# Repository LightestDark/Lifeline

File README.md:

# Lifeline

This project aims to expand on the existing LoRa Puck guide, to make a pair of fully functioning transmitters that can display messages from the latter via oled, provide accurate GPS location up to 2 meters and even vital info on moisture, temperature and pressure to make an esitmated guess on the weather at the area and relay it.

# Lessons

I LOVED the physics behind the why in the routing it actually linked so well to my own studies, especially the low pass filtering. Despite this being my smallest pcb to date by no means was it the easiest, with cramming as efficiently each component so there was enough room as well as keeping enough space to allow the RF components to work properly and juggle vias everywhere it was a labour.

# Assembly

Made a simple box with plently space for antennas and display

# PCB

Ensured short efficient tracks by precise placing of components

# Schematic

Added GPS, OLED and An array of sesnors packed into a BME280

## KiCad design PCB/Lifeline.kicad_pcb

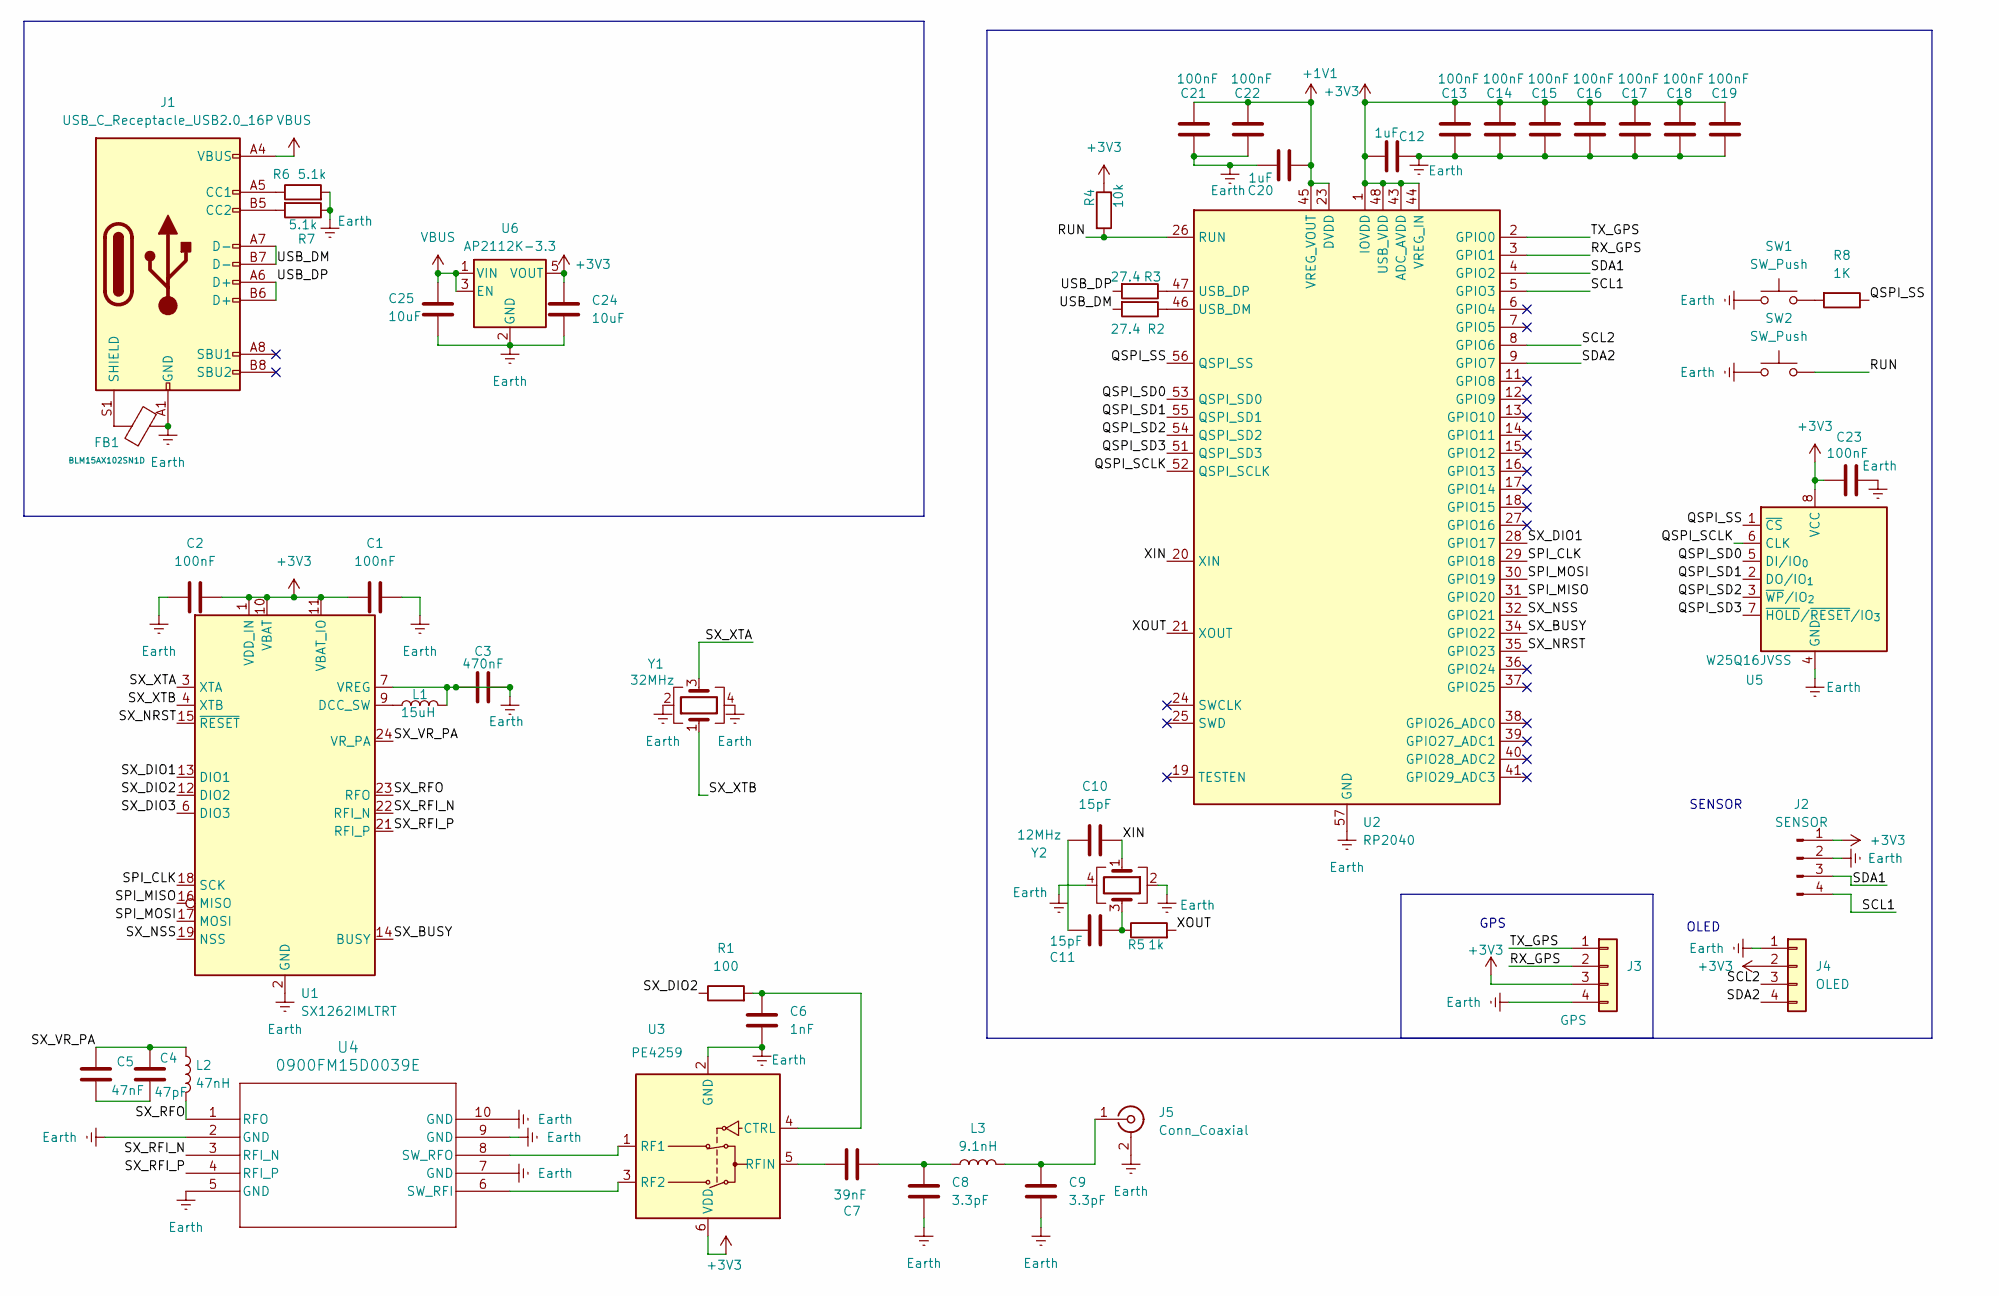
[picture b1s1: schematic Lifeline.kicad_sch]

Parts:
C1, C2, C13, C14, C15, C16, C17, C18, C19, C21, C22, C23: 100nF; C_0402_1005Metric
C3: 470nF; C_0402_1005Metric
C4: 47pF; C_0402_1005Metric
C5: 47nF; C_0402_1005Metric
C6: 1nF; C_0402_1005Metric
C7: 39nF; C_0402_1005Metric
C8, C9: 3.3pF; C_0402_1005Metric
C10, C11: 15pF; C_0402_1005Metric
C12, C20: 1uF; C_0402_1005Metric
C24, C25: 10uF; C_0402_1005Metric
FB1: BLM15AX102SN1D; L_0402_1005Metric; Current Rating 2A; Tolerance ±25%; Part BLM18PG121SN1D; LCSC C14709
J1: USB_C_Receptacle_USB2.0_16P; USB_C_Receptacle_GCT_USB4105-xx-A_16P_TopMnt_Horizontal
J2: SENSOR; PinHeader_1x04_P2.54mm_Vertical
J3: GPS; PinHeader_1x04_P2.54mm_Vertical
J4: OLED; PinSocket_1x04_P2.54mm_Vertical
J5: Conn_Coaxial; U.FL_Hirose_U.FL-R-SMT-1_Vertical
L1: 15uH; L_0402_1005Metric
L2: 47nH; L_0402_1005Metric
L3: 9.1nH; L_0402_1005Metric
R1: 100; R_0402_1005Metric
R2, R3: 27.4; R_0402_1005Metric
R4: 10k; R_0402_1005Metric
R5: 1k; R_0402_1005Metric
R6, R7: 5.1k; R_0402_1005Metric
R8: 1K; R_0402_1005Metric
SW1, SW2: SW_Push; SW_Tactile_SPST_NO_Straight_CK_PTS636Sx25SMTRLFS
U1: SX1262IMLTRT; QFN-24-1EP_4x4mm_P0.5mm_EP2.6x2.6mm
U2: RP2040; QFN-56-1EP_7x7mm_P0.4mm_EP3.2x3.2mm
U3: PE4259; SOT-363_SC-70-6
U4: 0900FM15D0039E; Balun_Johanson_0900FM15K0039
U5: W25Q16JVSS; SOIC-8_5.3x5.3mm_P1.27mm
U6: AP2112K-3.3; SOT-23-5
Y1: 32MHz; Crystal_SMD_3225-4Pin_3.2x2.5mm
Y2: 12MHz; Crystal_SMD_Abracon_ABM8G-4Pin_3.2x2.5mm

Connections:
+1V1: C20.2, C21.1, C22.1, U2.23 (DVDD), U2.45 (VREG_VOUT), U2.50 (DVDD)
+3V3: C1.1, C2.2, C12.1, C13.1, C14.1, C15.1, C16.1, C17.1, C18.1, C19.1, C23.1, C24.1, J2.1, J3.3, J4.2, R4.1, U1.1 (VDD_IN), U1.10 (VBAT), U1.11 (VBAT_IO), U2.1 (IOVDD), U2.10 (IOVDD), U2.22 (IOVDD), U2.33 (IOVDD), U2.42 (IOVDD), U2.43 (ADC_AVDD), U2.44 (VREG_IN), U2.48 (USB_VDD), U2.49 (IOVDD), U3.6 (VDD), U5.8 (VCC), U6.5 (VOUT)
/QSPI_SCLK: U2.52 (QSPI_SCLK), U5.6 (CLK)
/QSPI_SD0: U2.53 (QSPI_SD0), U5.5 (DI/IO_{0})
/QSPI_SD1: U2.55 (QSPI_SD1), U5.2 (DO/IO_{1})
/QSPI_SD2: U2.54 (QSPI_SD2), U5.3 (~WP/IO_{2})
/QSPI_SD3: U2.51 (QSPI_SD3), U5.7 (~HOLD/~RESET/IO_{3})
/QSPI_SS: R8.1, U2.56 (QSPI_SS), U5.1 (~CS)
/RUN: R4.2, SW2.2, U2.26 (RUN)
/RX_GPS: J3.2, U2.3 (GPIO1)
/SCL1: J2.4, U2.5 (GPIO3)
/SCL2: J4.3, U2.8 (GPIO6)
/SDA1: J2.3, U2.4 (GPIO2)
/SDA2: J4.4, U2.9 (GPIO7)
/SPI_CLK: U1.18 (SCK), U2.29 (GPIO18)
/SPI_MISO: U1.16 (MISO), U2.31 (GPIO20)
/SPI_MOSI: U1.17 (MOSI), U2.30 (GPIO19)
/SX_BUSY: U1.14 (BUSY), U2.34 (GPIO22)
/SX_DIO1: U1.13 (DIO1), U2.28 (GPIO17)
/SX_DIO2: R1.1, U1.12 (DIO2)
/SX_DIO3: U1.6 (DIO3)
/SX_NRST: U1.15 (~RESET), U2.35 (GPIO23)
/SX_NSS: U1.19 (NSS), U2.32 (GPIO21)
/SX_RFI_N: U1.22 (RFI_N), U4.3 (RFI_N)
/SX_RFI_P: U1.21 (RFI_P), U4.4 (RFI_P)
/SX_RFO: L2.2, U1.23 (RFO), U4.1 (RFO)
/SX_VR_PA: C4.1, C5.1, L2.1, U1.24 (VR_PA)
/SX_XTA: U1.3 (XTA), Y1.3
/SX_XTB: U1.4 (XTB), Y1.1
/TX_GPS: J3.1, U2.2 (GPIO0)
/USB_DM: J1.A7 (D-), J1.B7 (D-), R2.2
/USB_DP: J1.A6 (D+), J1.B6 (D+), R3.2
/XIN: C10.2, U2.20 (XIN), Y2.1
/XOUT: R5.2, U2.21 (XOUT)
Earth: C1.2, C2.1, C3.1, C3.2, C6.2, C8.2, C9.2, C12.2, C13.2, C14.2, C15.2, C16.2, C17.2, C18.2, C19.2, C20.1, C21.2, C22.2, C23.2, C24.2, C25.2, FB1.2, J1.A1 (GND), J1.A12 (GND), J1.B1 (GND), J1.B12 (GND), J2.2, J3.4, J4.1, J5.2 (Ext), L1.2, R6.2, R7.1, SW1.1, SW2.1, U1.2 (GND), U1.5 (GND), U1.7 (VREG), U1.8 (GND), U1.20 (GND), U1.25 (GND), U2.57 (GND), U3.2 (GND), U4.2 (GND), U4.5 (GND), U4.7 (GND), U4.9 (GND), U4.10 (GND), U5.4 (GND), U6.2 (GND), Y1.2, Y1.4, Y2.2, Y2.4
unnamed: C4.2, C5.2
unnamed: C7.2, C8.1, L3.1
unnamed: C10.1, C11.1
unnamed: C11.2, R5.1, Y2.3
unnamed: J1.A5 (CC1), R6.1
unnamed: J1.B5 (CC2), R7.2
unnamed: FB1.1, J1.S1 (SHIELD)
unnamed: C9.1, J5.1 (In), L3.2
unnamed: R8.2, SW1.2
unnamed: L1.1, U1.9 (DCC_SW)
unnamed: R2.1, U2.46 (USB_DM)
unnamed: R3.1, U2.47 (USB_DP)
unnamed: C6.1, R1.2, U3.4 (CTRL)
unnamed: U3.1 (RF1), U4.8 (SW_RFO)
unnamed: U3.3 (RF2), U4.6 (SW_RFI)
unnamed: C7.1, U3.5 (RFIN)
VBUS: C25.1, J1.A4 (VBUS), J1.A9 (VBUS), J1.B4 (VBUS), J1.B9 (VBUS), U6.1 (VIN), U6.3 (EN)

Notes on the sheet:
GPS
OLED
SENSOR

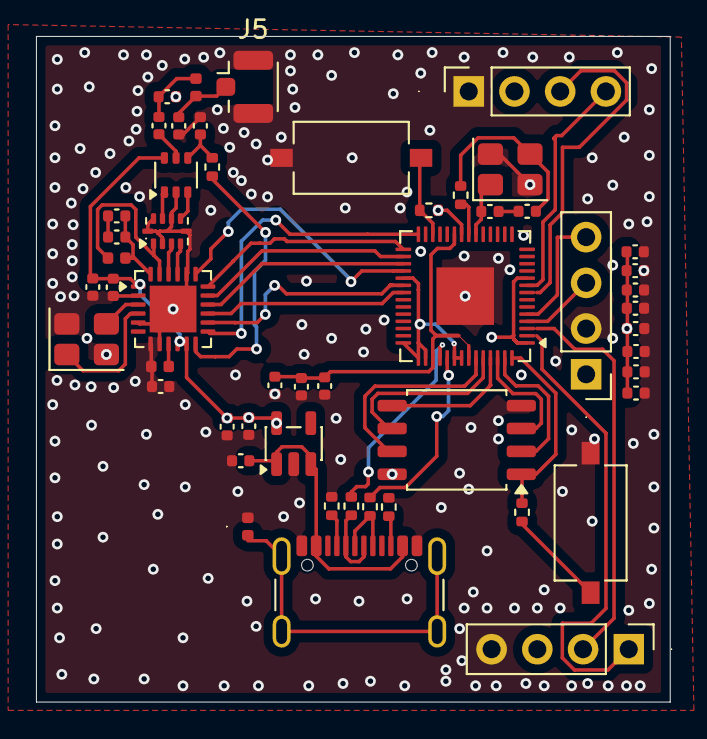
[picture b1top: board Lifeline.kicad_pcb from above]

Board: 4 copper layers, 35.2 x 37.0 mm, 52 parts (0 on the bottom side), 51 nets.

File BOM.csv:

"Reference","Qty","Value","DNP","Exclude from BOM","Exclude from Board","Footprint","Datasheet"
"C1,C2,C13,C14,C15,C16,C17,C18,C19,C21,C22,C23","12","100nF","","","","Capacitor_SMD:C_0402_1005Metric","~"
"C3","1","470nF","","","","Capacitor_SMD:C_0402_1005Metric","~"
"C4","1","47pF","","","","Capacitor_SMD:C_0402_1005Metric","~"
"C5","1","47nF","","","","Capacitor_SMD:C_0402_1005Metric","~"
"C6","1","1nF","","","","Capacitor_SMD:C_0402_1005Metric","~"
"C7","1","39nF","","","","Capacitor_SMD:C_0402_1005Metric","~"
"C8,C9","2","3.3pF","","","","Capacitor_SMD:C_0402_1005Metric","~"
"C10,C11","2","15pF","","","","Capacitor_SMD:C_0402_1005Metric","~"
"C12,C20","2","1uF","","","","Capacitor_SMD:C_0402_1005Metric","~"
"C24,C25","2","10uF","","","","Capacitor_SMD:C_0402_1005Metric","~"
"FB1","1","BLM15AX102SN1D","","","","Inductor_SMD:L_0402_1005Metric","https://www.lcsc.com/datasheet/lcsc_datasheet_2304140030_Mur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"
"J1","1","USB_C_Receptacle_USB2.0_16P","","","","Connector_USB:USB_C_Receptacle_GCT_USB4105-xx-A_16P_TopMnt_Horizontal","https://www.usb.org/sites/default/files/documents/usb_type-c.zip"
"J2","1","SENSOR","","","","Connector_PinHeader_2.54mm:PinHeader_1x04_P2.54mm_Vertical","~"
"J3","1","GPS","","","","Connector_PinHeader_2.54mm:PinHeader_1x04_P2.54mm_Vertical","~"
"J4","1","OLED","","","","Connector_PinSocket_2.54mm:PinSocket_1x04_P2.54mm_Vertical","~"
"J5","1","Conn_Coaxial","","","","Connector_Coaxial:U.FL_Hirose_U.FL-R-SMT-1_Vertical","~"
"L1","1","15uH","","","","Inductor_SMD:L_0402_1005Metric","~"
"L2","1","47nH","","","","Inductor_SMD:L_0402_1005Metric","~"
"L3","1","9.1nH","","","","Inductor_SMD:L_0402_1005Metric","~"
"R1","1","100","","","","Resistor_SMD:R_0402_1005Metric","~"
"R2,R3","2","27.4","","","","Resistor_SMD:R_0402_1005Metric","~"
"R4","1","10k","","","","Resistor_SMD:R_0402_1005Metric","~"
"R5","1","1k","","","","Resistor_SMD:R_0402_1005Metric","~"
"R6,R7","2","5.1k","","","","Resistor_SMD:R_0402_1005Metric","~"
"R8","1","1K","","","","Resistor_SMD:R_0402_1005Metric","~"
"SW1,SW2","2","SW_Push","","","","Button_Switch_SMD:SW_Tactile_SPST_NO_Straight_CK_PTS636Sx25SMTRLFS","~"
"U1","1","SX1262IMLTRT","","","","Package_DFN_QFN:QFN-24-1EP_4x4mm_P0.5mm_EP2.6x2.6mm","https://semtech.file.force.com/sfc/dist/version/download/?oi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"
"U2","1","RP2040","","","","Package_DFN_QFN:QFN-56-1EP_7x7mm_P0.4mm_EP3.2x3.2mm","https://datasheets.raspberrypi.com/rp2040/rp2040-datasheet.pdf"
"U3","1","PE4259","","","","Package_TO_SOT_SMD:SOT-363_SC-70-6","https://lcsc.com/datasheet/lcsc_datasheet_2409301504_pSemi-P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"
"U4","1","0900FM15D0039E","","","","RF_Converter:Balun_Johanson_0900FM15K0039","0900FM15D0039E"
"U5","1","W25Q16JVSS","","","","Package_SO:SOIC-8_5.3x5.3mm_P1.27mm","https://www.winbond.com/hq/support/documentation/levelOne.js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"
"U6","1","AP2112K-3.3","","","","Package_TO_SOT_SMD:SOT-23-5","https://www.diodes.com/assets/Datasheets/AP2112.pdf"
"Y1","1","32MHz","","","","Crystal:Crystal_SMD_3225-4Pin_3.2x2.5mm","~"
"Y2","1","12MHz","","","","Crystal:Crystal_SMD_Abracon_ABM8G-4Pin_3.2x2.5mm","~"

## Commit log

2026-01-08 Create Code
